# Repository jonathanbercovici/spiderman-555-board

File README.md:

# spiderman-555-board
my first attempt at a cool spideraman themed board

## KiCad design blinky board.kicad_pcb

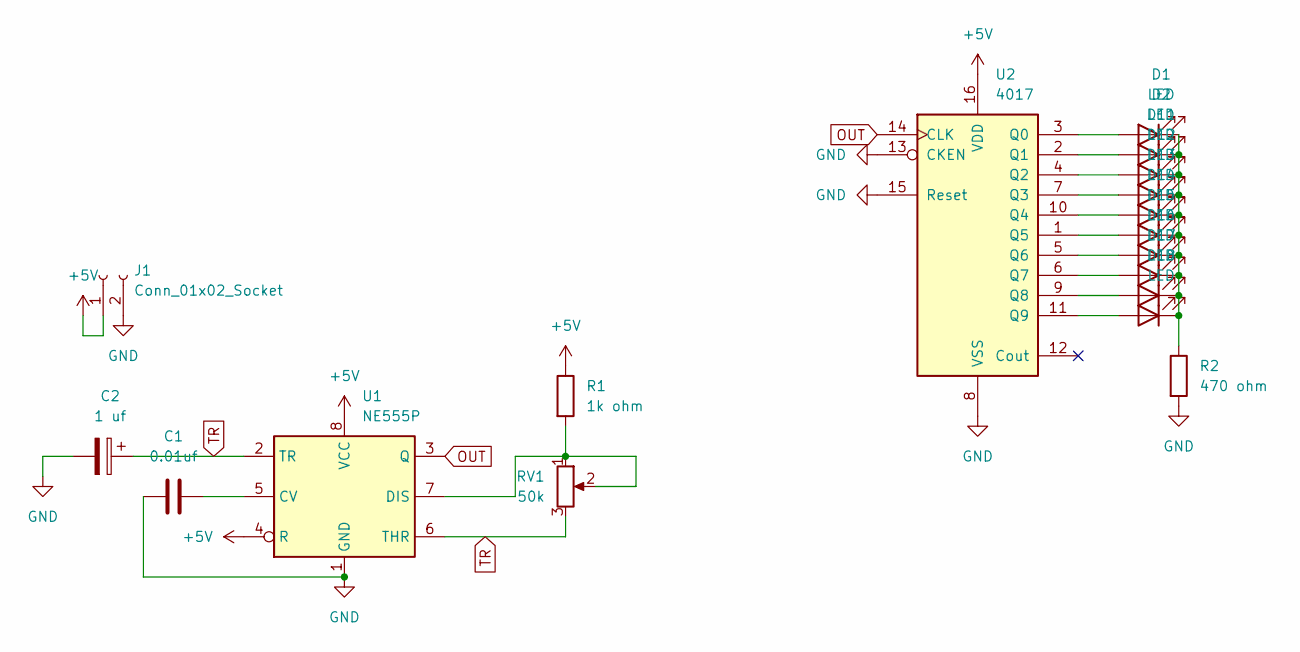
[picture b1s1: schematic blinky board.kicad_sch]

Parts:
C1: 0.01uf; CP_Radial_D5.0mm_P2.00mm
C2: 1 uf; C_Disc_D7.5mm_W2.5mm_P5.00mm
D1, D2, D11, D12, D13, D14, D15, D16, D17, D18: LED; LED_D3.0mm
J1: Conn_01x02_Socket; PinHeader_1x02_P2.54mm_Vertical
R1: 1k ohm; R_Axial_DIN0207_L6.3mm_D2.5mm_P7.62mm_Horizontal
R2: 470 ohm; R_Axial_DIN0207_L6.3mm_D2.5mm_P7.62mm_Horizontal
RV1: 50k; Potentiometer_Vishay_T93YA_Vertical
U1: NE555P; DIP-8_W7.62mm
U2: 4017; N16

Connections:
+5V: J1.1, R1.1, U1.4 (R), U1.8 (VCC), U2.16 (VDD)
GND: C1.1, C2.2, J1.2, R2.2, U1.1 (GND), U2.8 (VSS), U2.13 (CKEN), U2.15 (Reset)
unnamed: D1.2 (A), U2.3 (Q0)
unnamed: D1.1 (K), D2.1 (K), D11.1 (K), D12.1 (K), D13.1 (K), D14.1 (K), D15.1 (K), D16.1 (K), D17.1 (K), D18.1 (K), R2.1
unnamed: D2.2 (A), U2.2 (Q1)
unnamed: D11.2 (A), U2.4 (Q2)
unnamed: D12.2 (A), U2.7 (Q3)
unnamed: D13.2 (A), U2.10 (Q4)
unnamed: D14.2 (A), U2.1 (Q5)
unnamed: D15.2 (A), U2.5 (Q6)
unnamed: D16.2 (A), U2.6 (Q7)
unnamed: D17.2 (A), U2.9 (Q8)
unnamed: D18.2 (A), U2.11 (Q9)
unnamed: C1.2, U1.5 (CV)
unnamed: R1.2, RV1.1, RV1.2, U1.7 (DIS)
OUT: U1.3 (Q), U2.14 (CLK)
TR: C2.1, RV1.3, U1.2 (TR), U1.6 (THR)

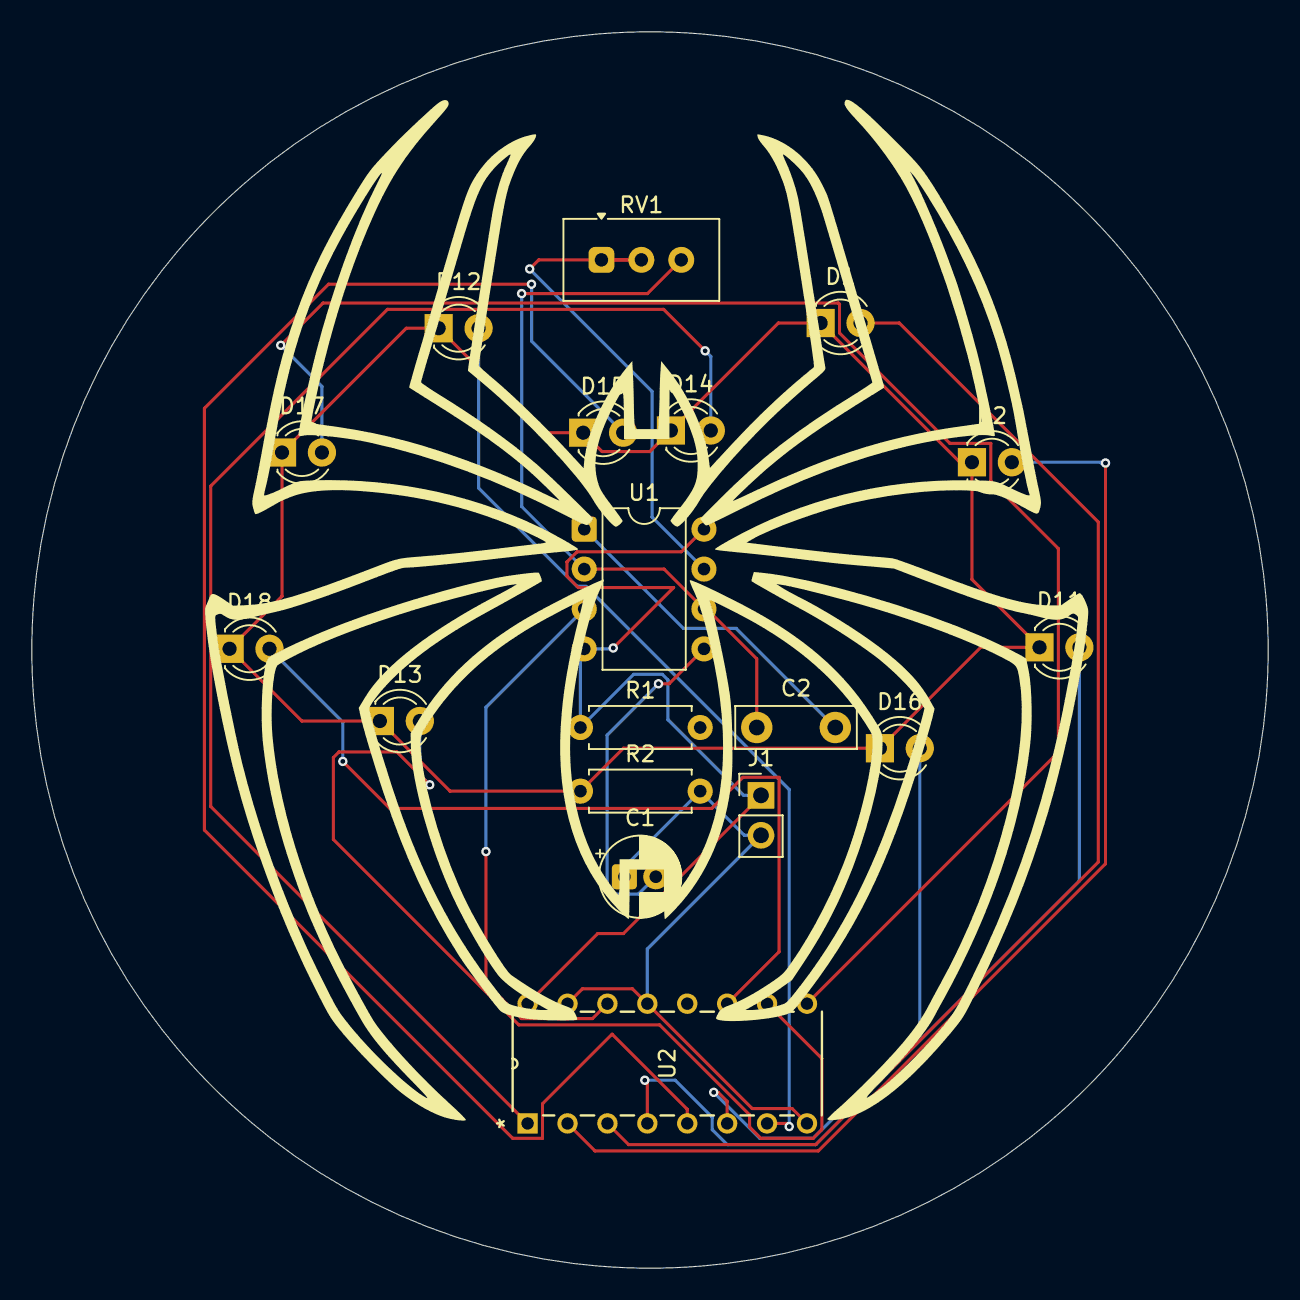
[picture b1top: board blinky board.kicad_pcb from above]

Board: 2 copper layers, 78.7 x 78.7 mm, 18 parts (0 on the bottom side), 17 nets.
